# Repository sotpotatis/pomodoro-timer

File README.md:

# Pomodoro Timer

## What is this?

This Project aims to create a portable Pomodoro timer that you can carry around with you - regardless if studying in the library, on the bus, or in the Comfort of your own home!

### Components and technology

#### Programming languages

The main part of this Project is programmed in AVR Assembly. Some parts are coded in C.

#### Main Components used

* Attiny84A

* DS3231 timer

#### Building the Circuit/assembling the PCB

For the full description on how to build the Project, I will at some Point (**TODO**) provide documentation about how to assemble your own Pomodoro timer.

## Development

Under the `code` folder you will find a solution which you can import into Microchip Studio (version 7).

You also need to add the files `i2cmaster.h` and `i2cmaster.S` which are from Peter Fleury's I2CMaster library (can be found [here](http://www.peterfleury.epizy.com/avr-software.html?i=1))

Inside `tests` you will find various tests carried out during the project - please see the `README` inside that directory.

## Documentation

See the `docs` folder for Project documentation.

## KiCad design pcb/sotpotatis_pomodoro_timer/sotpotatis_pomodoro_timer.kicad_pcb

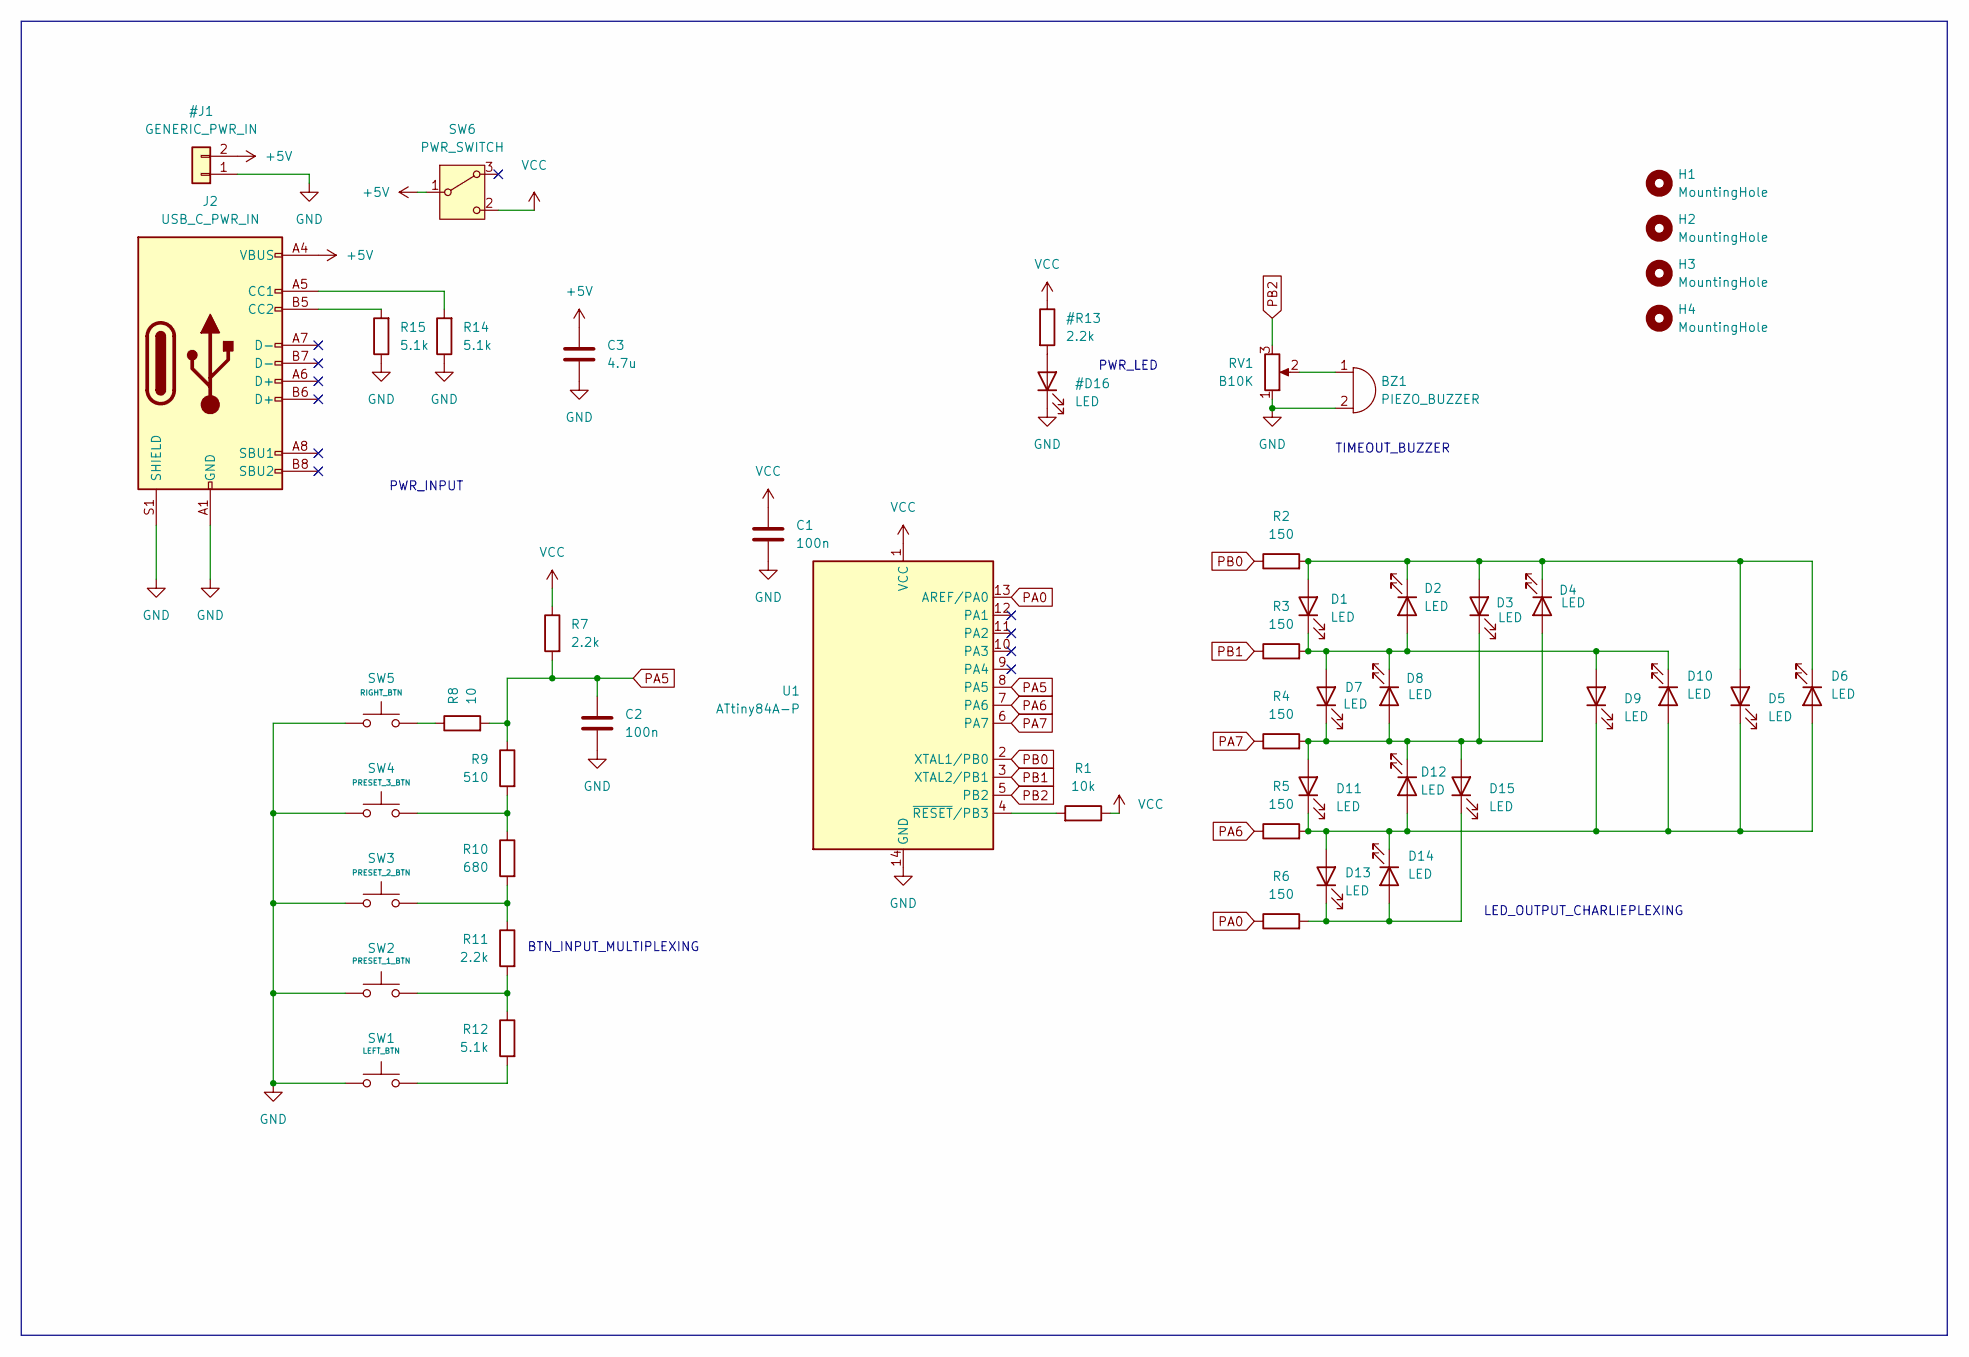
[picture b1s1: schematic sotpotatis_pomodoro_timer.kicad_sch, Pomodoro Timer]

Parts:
BZ1: PIEZO_BUZZER; Buzzer_12x5.5RM6.5
C1, C2: 100n; C_0805_2012Metric_Pad1.18x1.45mm_HandSolder
C3: 4.7u; C_0805_2012Metric_Pad1.18x1.45mm_HandSolder
D1, D2, D3, D4, D5, D6, D7, D8, D9, D10, D11, D12, D13, D14, D15: LED; LED_D3.0mm
H1, H2, H3, H4: MountingHole; MountingHole_3.2mm_M3
J2: USB_C_PWR_IN; USB_C_Receptacle_HRO_TYPE-C-31-M-12
R1: 10k; R_0805_2012Metric_Pad1.20x1.40mm_HandSolder
R2, R3, R4, R5, R6: 150; R_0805_2012Metric_Pad1.20x1.40mm_HandSolder
R7, R11: 2.2k; R_0805_2012Metric_Pad1.20x1.40mm_HandSolder
R8: 10; R_0805_2012Metric_Pad1.20x1.40mm_HandSolder
R9: 510; R_0805_2012Metric_Pad1.20x1.40mm_HandSolder
R10: 680; R_0805_2012Metric_Pad1.20x1.40mm_HandSolder
R12, R14, R15: 5.1k; R_0805_2012Metric_Pad1.20x1.40mm_HandSolder
RV1: B10K; Potentiometer_Bourns_3386P_Vertical
SW1: LEFT_BTN; SW_PUSH_6mm_H5mm
SW2: PRESET_1_BTN; SW_PUSH_6mm_H5mm
SW3: PRESET_2_BTN; SW_PUSH_6mm_H5mm
SW4: PRESET_3_BTN; SW_PUSH_6mm_H5mm
SW5: RIGHT_BTN; SW_PUSH_6mm_H5mm
SW6: PWR_SWITCH; SW_Slide-03_Wuerth-WS-SLTU_10x2.5mm_P2.54mm
U1: ATtiny84A-P; DIP-14_W7.62mm_Socket

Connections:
unnamed: BZ1.1 (+), RV1.2
unnamed: D1.2 (A), D2.1 (K), D3.2 (A), D4.1 (K), D5.2 (A), D6.1 (K), R2.2
unnamed: D1.1 (K), D2.2 (A), D7.2 (A), D8.1 (K), D9.2 (A), D10.1 (K), R3.2
unnamed: D5.1 (K), D6.2 (A), D9.1 (K), D10.2 (A), D11.1 (K), D12.2 (A), D13.2 (A), D14.1 (K), R5.2
unnamed: D3.1 (K), D4.2 (A), D7.1 (K), D8.2 (A), D11.2 (A), D12.1 (K), D15.2 (A), R4.2
unnamed: D13.1 (K), D14.2 (A), D15.1 (K), R6.2
unnamed: J2.A5 (CC1), R14.2
unnamed: J2.B5 (CC2), R15.2
unnamed: R8.1, SW5.1
unnamed: R9.2, R10.1, SW4.1
unnamed: R10.2, R11.1, SW3.1
unnamed: R11.2, R12.1, SW2.1
unnamed: R12.2, SW1.1
unnamed: R1.2, U1.4 (~RESET/PB3)
PA0: R6.1, U1.13 (AREF/PA0)
PA5: C2.1, R7.2, R8.2, R9.1, U1.8 (PA5)
PA6: R5.1, U1.7 (PA6)
PA7: R4.1, U1.6 (PA7)
PB0: R2.1, U1.2 (XTAL1/PB0)
PB1: R3.1, U1.3 (XTAL2/PB1)
PB2: RV1.3, U1.5 (PB2)

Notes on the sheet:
PWR_LED
BTN_INPUT_MULTIPLEXING
LED_OUTPUT_CHARLIEPLEXING
PWR_INPUT
TIMEOUT_BUZZER

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
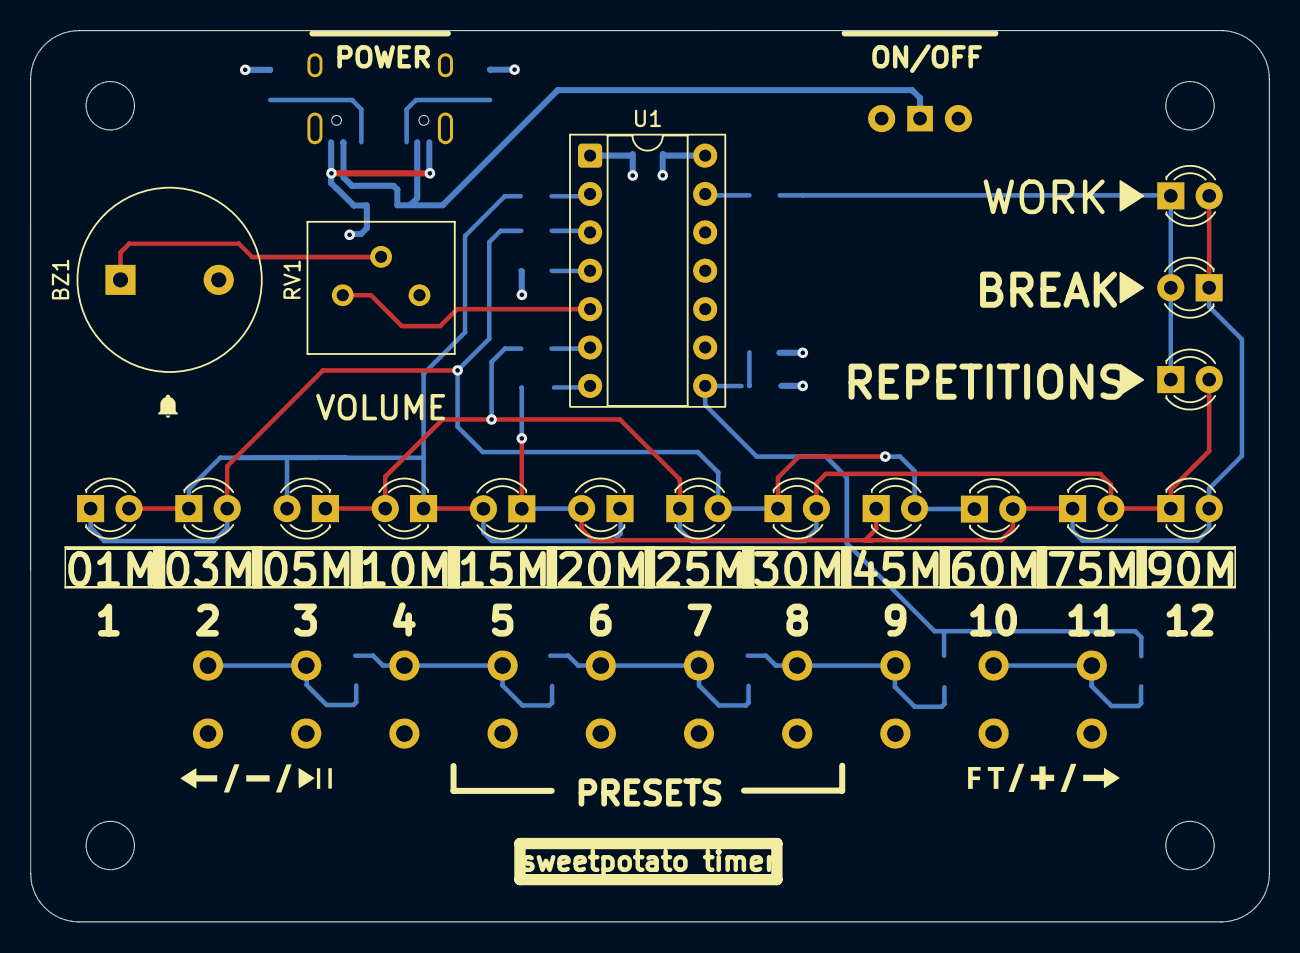
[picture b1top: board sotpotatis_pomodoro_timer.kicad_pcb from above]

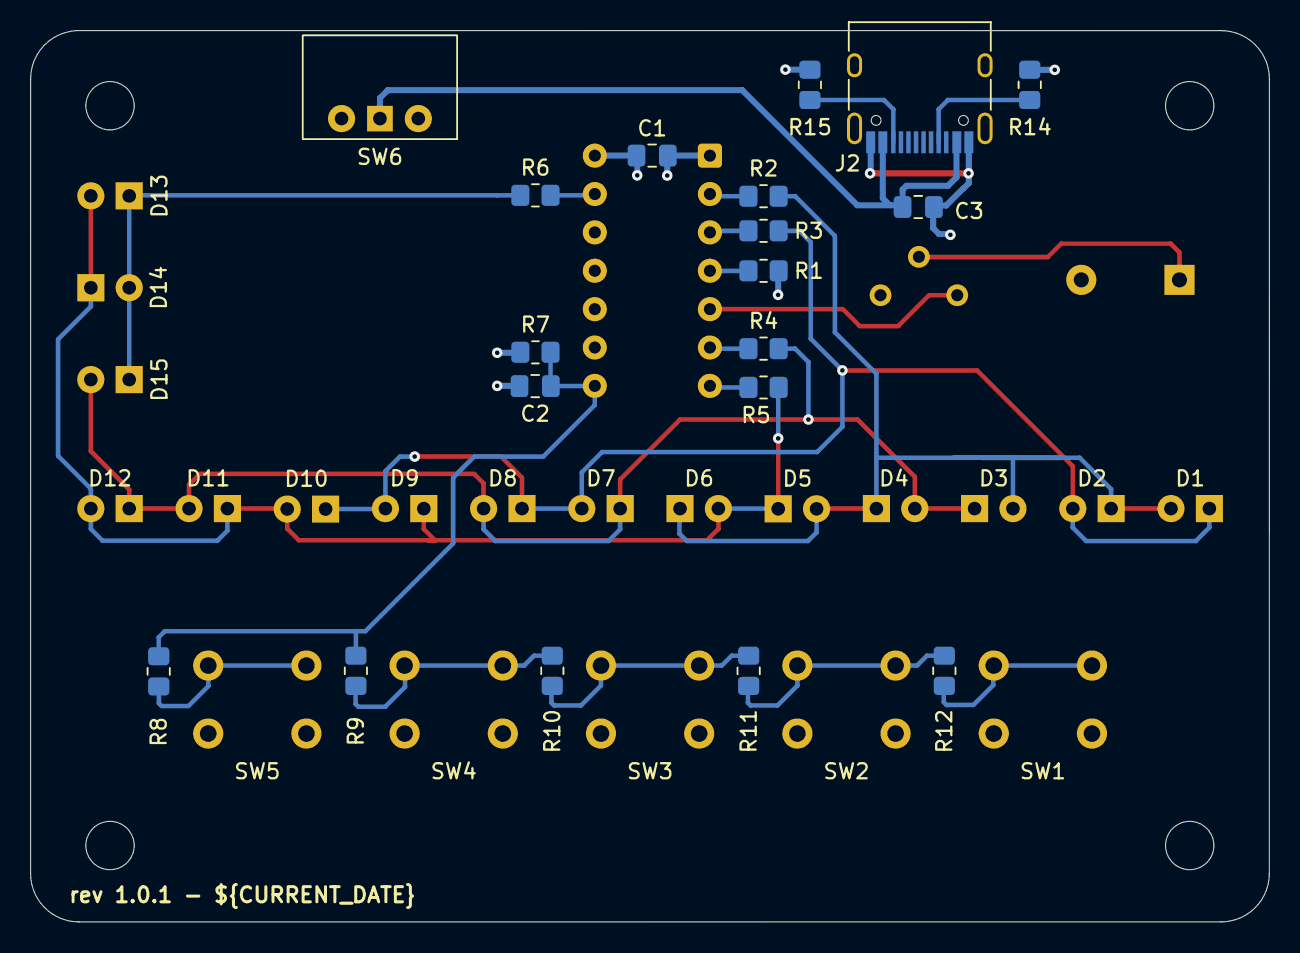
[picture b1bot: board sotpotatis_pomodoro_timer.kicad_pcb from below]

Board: 4 copper layers, 82.0 x 59.0 mm, 47 parts (19 on the bottom side), 24 nets.

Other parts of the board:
LB2: LOGO

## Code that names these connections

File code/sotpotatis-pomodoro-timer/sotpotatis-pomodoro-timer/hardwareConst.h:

/* hardwareConst.h
Defines hardware-related constants.
*/
#include <avr/io.h>
#ifndef HARDWARECONST_H_
	#define HARDWARECONST_H_
		// This is part of <avr/io.h> and we need to redefine this for proper I/O address referencing
		#undef __SFR_OFFSET
		#define __SFR_OFFSET  0
		// ====== ADC Pin to use for button multiplexing ======
		// Note that ADC pins simply use the format defined by Microchip
		// (0-7 depending on if you want to use pin PA0-7)
		#define BUTTON_ADC_PIN 5
		// For Pure I/O pins (not ADC-pins), each "_PIN" definition follows the following format:
		// The Attiny24A has 12 GPIO pins. Starting from PA we define a 16 bit number:
		// 0bPA7|PA6....PA0|constant 0000 PB3|...PB0 (for example: 0b0000 0011 0000 0000 refers to PA0 and PA1)
		// Where one and only one bit is high to control one pin.
		// For instance, 0b0000 0001 0000 maps a label to PA0.
		// It points to a 2x integer list where the first element represents:
		// 0: The pin is connected to PORTA, 1: The pin is connected to PORTB
		// And the next entry in the list is the actual pin that is being used.
		// ====== LED pins ======
		// Note that we use LED Charlieplexing, so that one
		// pin controls 3 LEDs. The format of pin numbers is according to above,
		// that is why we left shift by 8.
		#define LED_CHARLIEPLEXING_PIN_1 0x0001 // PB0
		#define LED_CHARLIEPLEXING_PIN_2 0x0002 // PB1
		#define LED_CHARLIEPLEXING_PIN_3 0x8000 // PA7
		#define LED_CHARLIEPLEXING_PIN_4 0x4000 // PA6
		#define LED_CHARLIEPLEXING_PIN_5 0x0100// PA0
		// Operates only on 8 bit registers
		#define PA_PIN_MASK 0xFF
		#define PB_PIN_MASK 0x0F
#endif 

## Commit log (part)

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2025-01-19 add: Initial commit
2025-01-20 Fix README format
2025-01-23 add: Progress dump of (seemingly working) pin state functions
2025-02-02 add: Recent Charlieplexing attempts
2025-02-02 refactor: Move schematics for Charlieplexing tests to subfolder
2025-03-04 add: Charlieplexing code backup, works for PIN0 only
2025-03-05 Update Charlieplexing loop to work in more cases
2025-03-05 add: Lift some code outside of the loop in ledHandlers.S
2025-03-30 fix: Fully working Charlieplexing proof of concept!
2025-05-19 add: ADC interrupts working!
2025-05-30 fix: Interrupts weren't properly coded. Now they are!
2025-06-02 add: Working timer interrupts!
2025-06-12 add: Seeming working ADC multiplexing code
2025-06-12 fix: Reduce timing of hold
2025-06-12 add: Tests for ADC multiplexing
2025-06-12 fix: Several cleanups across the whole project
2025-06-14 fix: Cleanups across the whole code. Make tap detection have an upper limit.
2025-06-14 fix: Formatting update of header files
2025-06-14 add: EEPROM library & simple example
2025-06-19 fix: Ensure local copy of ADC value is used
2025-06-19 fix: Small comment fixes
2025-06-21 add: ADC Multiplexing function now in ASM
2025-06-23 fix: Move old ADC Multiplexing code in C to its own file
2025-06-23 add: Charlieplexing for 15 LEDs tests
2025-06-23 add: Charlieplex 15 LEDs. Add buzzer proof of concept.
2025-06-23 docs: Give credit for button multiplexing algorithm
2025-06-30 add: Timer calibration-related code
2025-06-30 docs: Fix spelling mistake in docstring
2025-06-30 docs: Add initial version of docs, which mention timer calibration
2025-06-30 docs: Minor formatting change
2025-07-04 add: First draft of Charlieplexing added to schematic
2025-07-04 fix: Remove temp & backup KiCad files from repo
2025-07-04 fix: Accidentally deleted a whole folder in prev commit
2025-07-07 add: ADC input pin multiplexing added to PCB
2025-07-10 add: Buzzer testing...
2025-07-11 fix: Buzzer rattlin' by using output compare pins instead
2025-07-11 fix: Toggle output compare pin for buzzer via timer register instead of pin state
2025-07-16 add: Initial version (0.1) of final schematics
2025-07-16 add: Update schematic according to online feedback (v0.2)
2025-07-19 add: Current-limiting resistor to PCB (v0.2)
2025-07-19 fix: ADC multiplexing values were for pullup of 2k instead of 2.2k
2025-07-21 fix: Change constants to match final PCB pin usage
2025-07-21 fix: Humming when buzzer was not playing
2025-07-21 add: USB-C power input (schematics rev 0.3)
2025-07-25 add: Fix footprints in PCB, start setting up DRC settings
2025-07-26 add: Finalize DRC settings, switch to 4-layer
2025-08-04 add: Backup PCB progress. Working with placement.
2025-08-05 add: Layout variant 1 of PCB
2025-08-05 add: Layout variant 2 of PCB
2025-08-05 add: Layout variant 3 of PCB
2025-08-07 add: Backup progress with updated variant 1 PCB
2025-08-09 add: Update component placement (primarily switch+LED centering) of PCB variant 1
2025-10-21 add: Final component placement (except SMD) for PCB
2025-10-22 fix: Remove 1M shield resistor, component relabels for better layout
2025-10-24 add: Backup spaghetti Charlieplexing wiring :)
2026-01-20 add: Backup PCB routing progress before board reversal...
2026-01-20 add: Route everything but buzzer (No reversal needed)
2026-02-04 fix: Finish silkscreen time scale for LEDs
2026-02-27 fix: Some silkscreen labels positioned wrong + round off board edge
2026-03-25 fix: All silkscreen labels except the logo is now exactly where they should for prod.
2026-04-04 fix: Small changes to silkscreen & component placement to make board look clearer
2026-04-04 fix: Update board, probably ready for prod
2026-05-28 add: PCB rev1.0.1: all components on one side to cut down assembly costs
